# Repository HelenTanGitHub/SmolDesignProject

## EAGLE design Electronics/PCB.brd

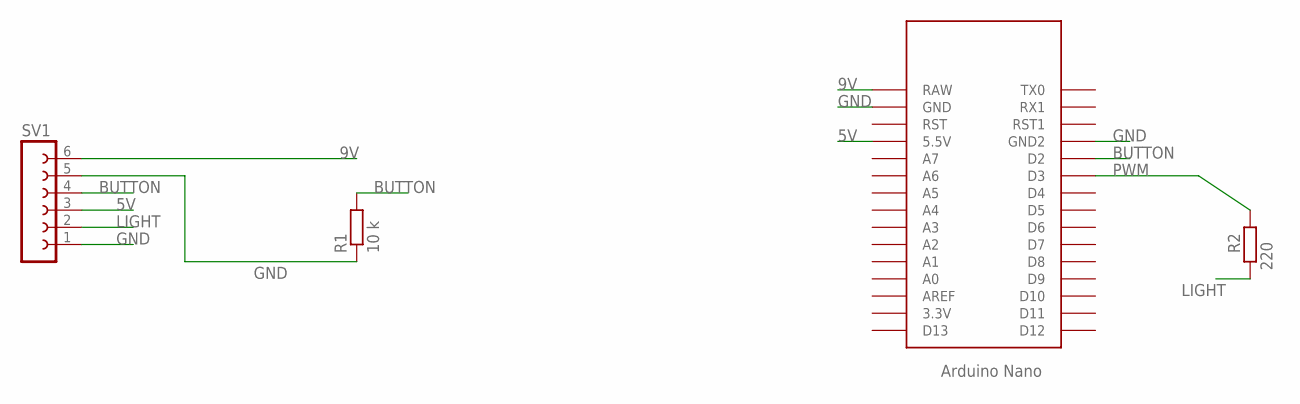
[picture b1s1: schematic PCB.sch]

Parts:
R1: 10 k; R0805
R2: 220; R0805
SV1: FE06-1; FE06
U$1: NANO

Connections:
5V: SV1.3, U$1.5V (5.5V)
9V: SV1.6, U$1.RAW
BUTTON: R1.2, SV1.4, U$1.D2
GND: R1.1, SV1.1, SV1.5, U$1.GND, U$1.GND1 (GND2)
LIGHT: R2.1, SV1.2
PWM: R2.2, U$1.D3

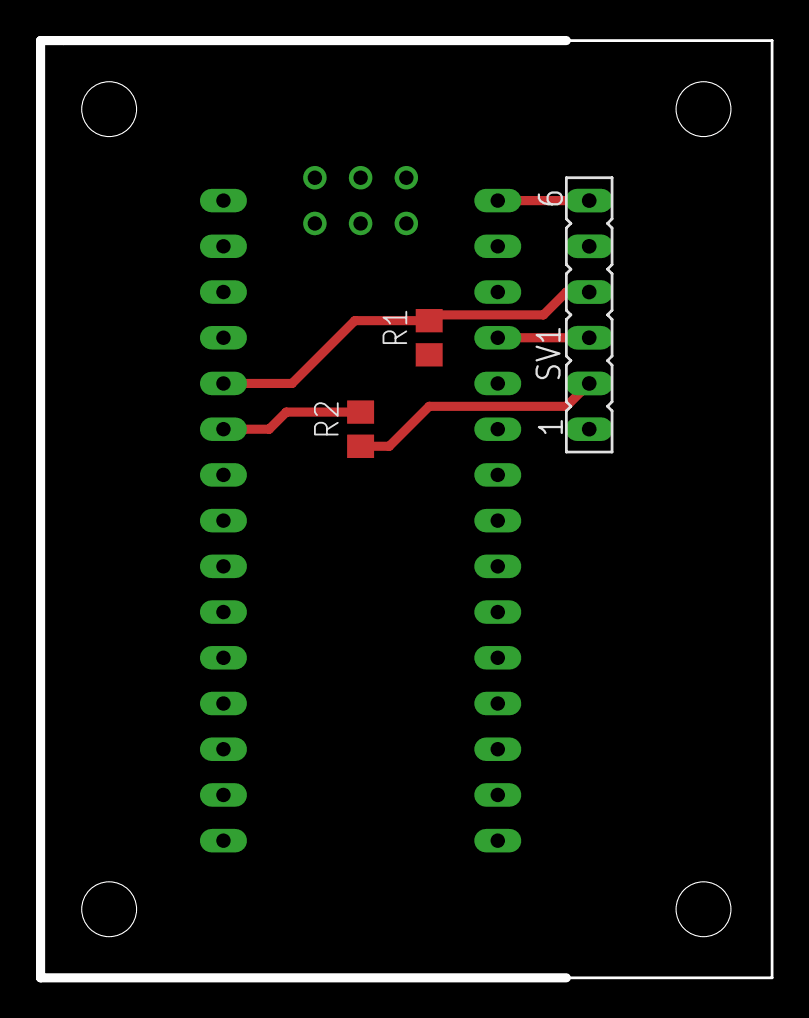
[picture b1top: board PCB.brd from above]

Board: 2 copper layers, 40.5 x 52.1 mm, 4 parts (0 on the bottom side), 6 nets.

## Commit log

2018-11-01 Rough sketch of electronics circuit schematic
2018-11-01 made Electronics File
2018-11-19 uploaded PCB and schematic
2018-11-19 picture version of pcb
2018-11-21 changed traces to 20 mills
2018-11-26 removed regulator, changed some pins for better routing
2018-11-27 Arduino Code v1
2018-12-03 working and tested Arduino Code
2018-12-03 Final PCB Design
2018-12-06 forgot GND polygon
2018-12-09 mechanical enclosure files
